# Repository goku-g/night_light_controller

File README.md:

# Night light control system based on PIR sensor and ESP32.

A clone version of the project done by @alphaseneca. Initial project link: https://github.com/alphaseneca/stairlight_controller/tree/master

## Schematic

## PCB Layout

## Live Preview

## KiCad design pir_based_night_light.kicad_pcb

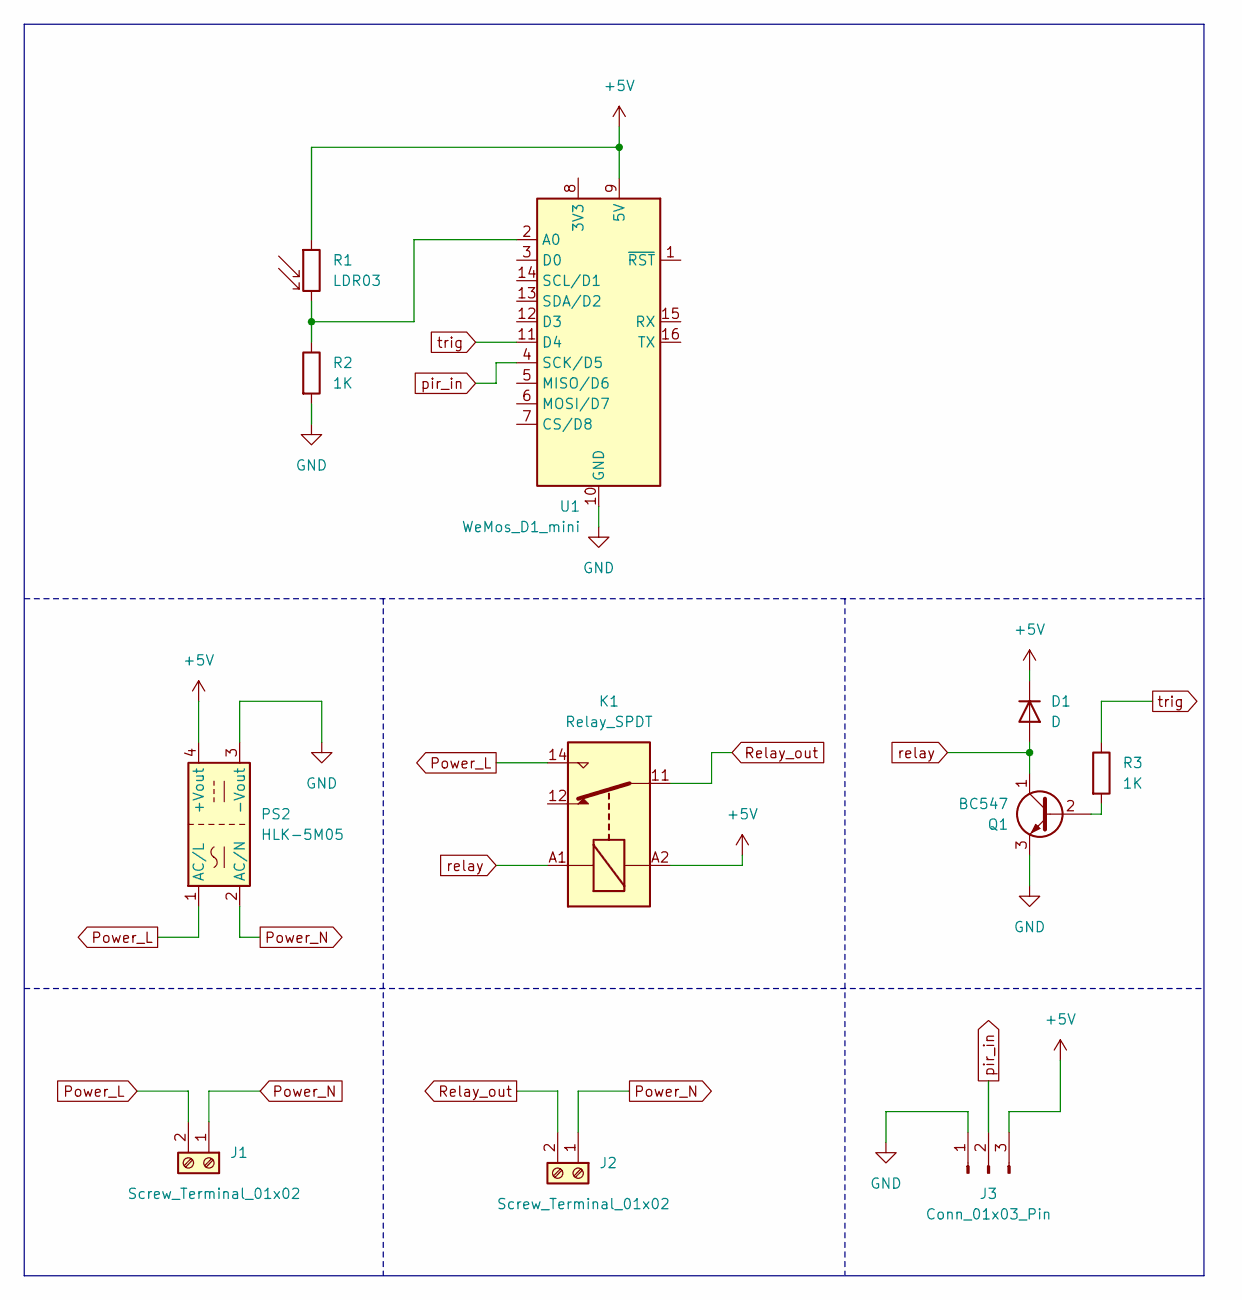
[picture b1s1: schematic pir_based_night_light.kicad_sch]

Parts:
D1: D; D_5W_P12.70mm_Horizontal
J1, J2: Screw_Terminal_01x02; TE_282837-2
J3: Conn_01x03_Pin; PinHeader_1x03_P2.54mm_Vertical
K1: Relay_SPDT; Relay_SPDT_Finder_36.11
PS2: HLK-5M05; CONV_HLK-5M05
Q1: BC547; TO-92_Inline
R1: LDR03; R_LDR_10x8.5mm_P7.6mm_Vertical
R2, R3: 1K; R_Axial_DIN0207_L6.3mm_D2.5mm_P10.16mm_Horizontal
U1: WeMos_D1_mini; WEMOS_D1_mini_light

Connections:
+5V: D1.1 (K), J3.3, K1.A2, PS2.4 (+Vout), R1.1, U1.9 (5V)
GND: J3.1, PS2.3 (-Vout), Q1.3 (E), R2.2, U1.10 (GND)
unnamed: Q1.2 (B), R3.2
unnamed: R1.2, R2.1, U1.2 (A0)
Power_L: J1.2, K1.14, PS2.1 (AC/L)
Power_N: J1.1, J2.1, PS2.2 (AC/N)
Relay_out: J2.2, K1.11
pir_in: J3.2, U1.4 (SCK/D5)
relay: D1.2 (A), K1.A1, Q1.1 (C)
trig: R3.1, U1.11 (D4)

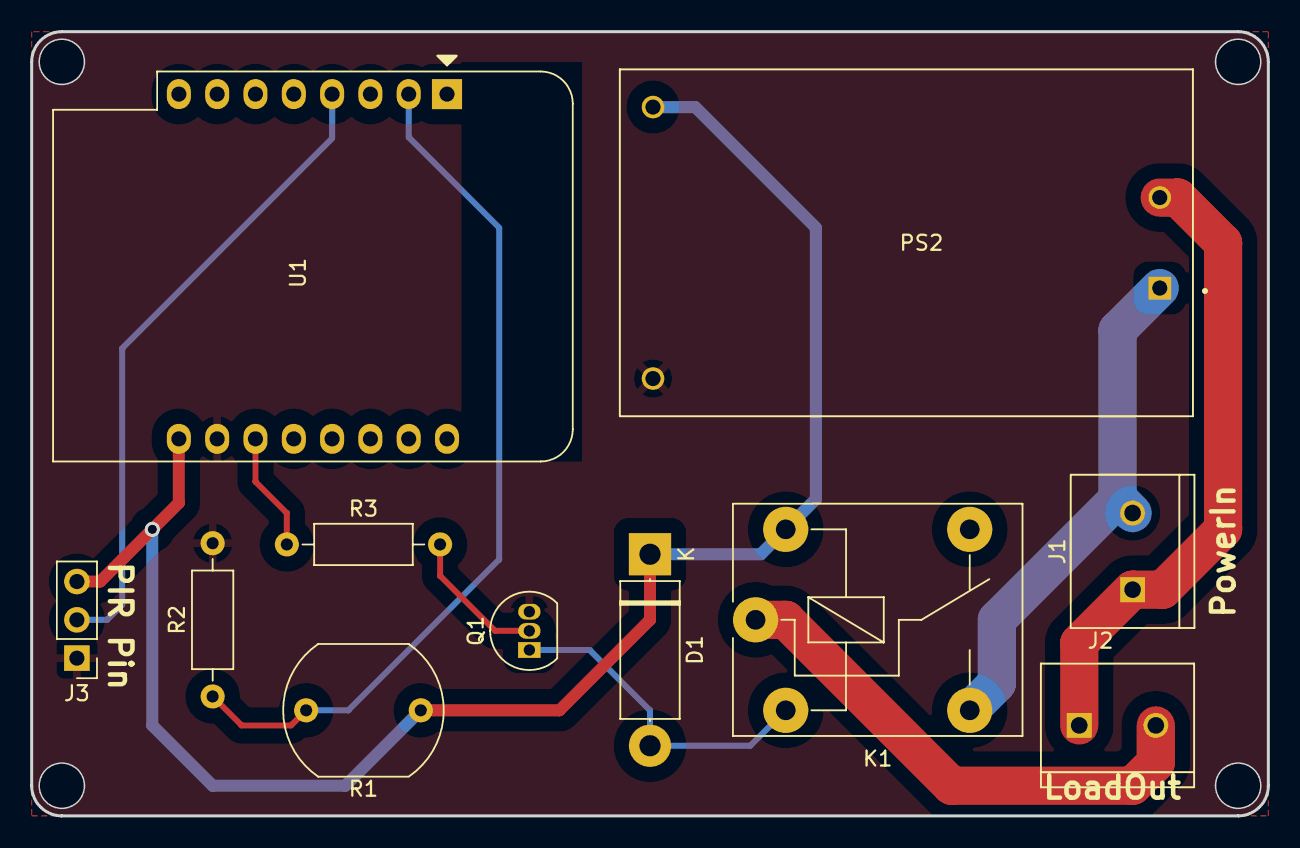
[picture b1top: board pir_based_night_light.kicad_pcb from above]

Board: 2 copper layers, 82.0 x 52.0 mm, 11 parts (0 on the bottom side), 10 nets.

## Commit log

2023-11-16 schematic, pcb layout for the system
2023-11-16 images for preview
2023-11-16 touch up
2024-04-11 change
